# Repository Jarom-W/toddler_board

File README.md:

# Toddler Activity Board

All the files you'd need to 3D print the components, program the hardware, and order the exact PCB I used.

## Some project specifications:

### Hardware
- ESP32 Dev Module

### 3D Printing
- Bambu Lab A1 using standard PLA filament

### Screws
- I used a few different sized screws which I sourced from this lot https://www.amazon.com/dp/B089QX453K?ref=ppx_yo2ov_dt_b_fed_asin_title

### Power Supply
- 4 AA Batteries held inside a battery pack providing ~5V DC to the ESP32 module

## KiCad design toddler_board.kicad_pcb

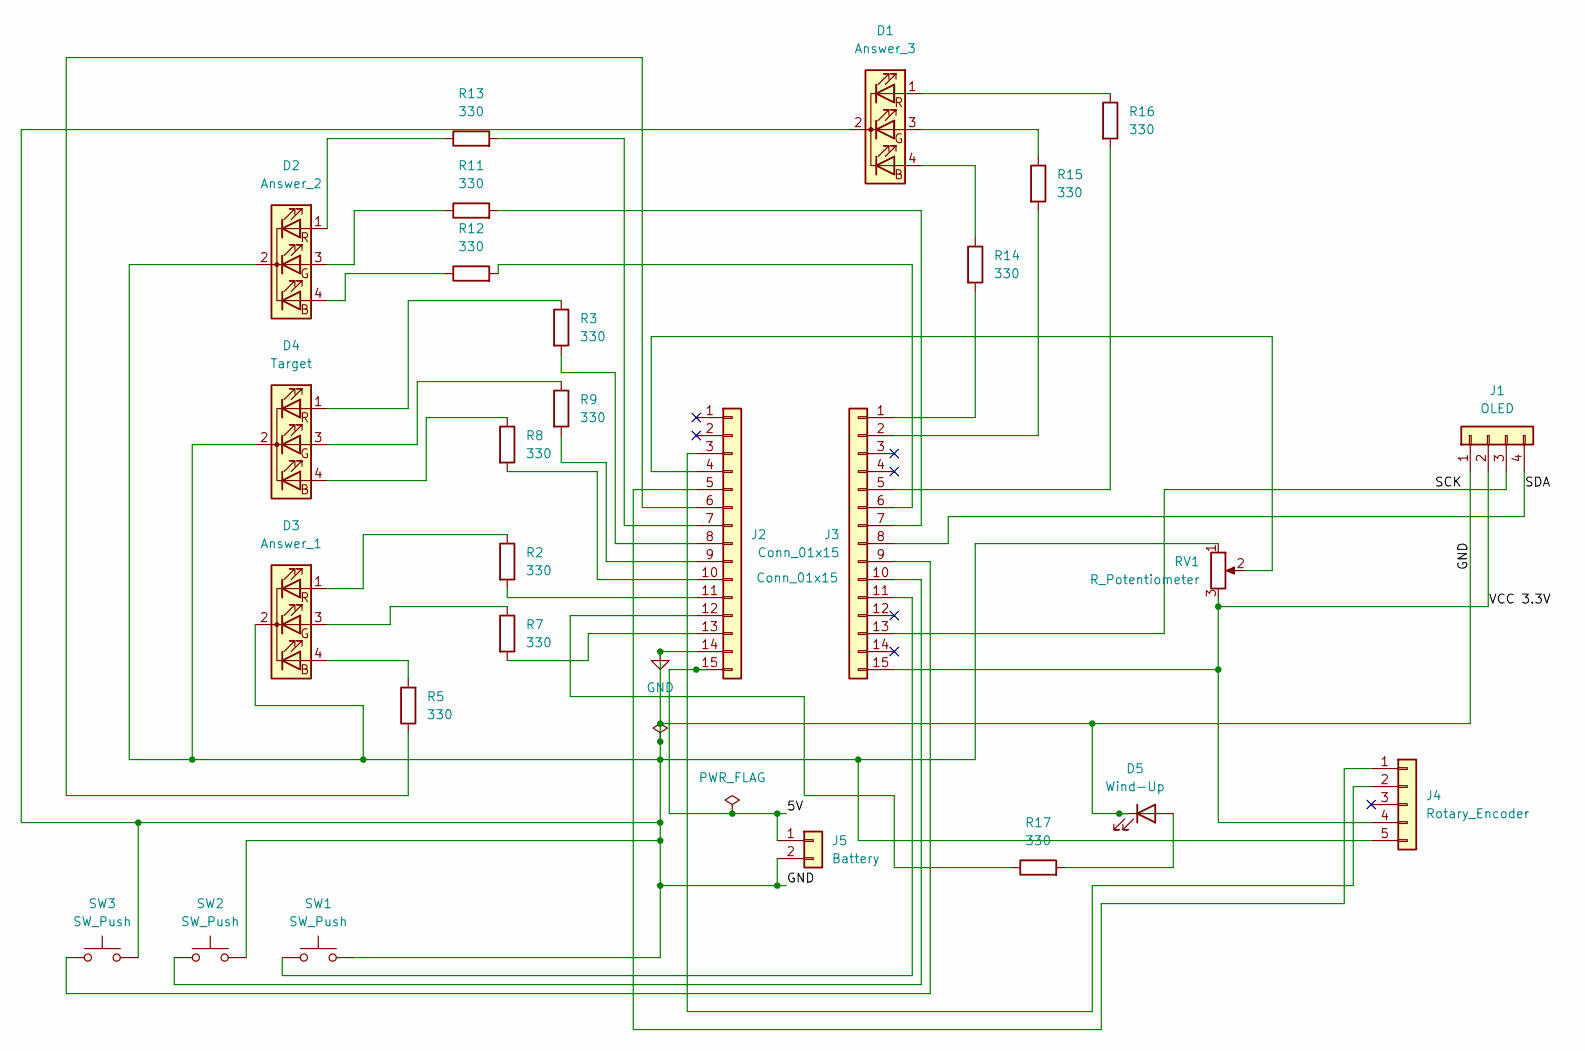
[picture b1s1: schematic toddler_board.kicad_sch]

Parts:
D1: Answer_3; LED_D5.0mm-4_RGB_Wide_Pins
D2: Answer_2; LED_D5.0mm-4_RGB_Wide_Pins
D3: Answer_1; LED_D5.0mm-4_RGB_Wide_Pins
D4: Target; LED_D5.0mm-4_RGB_Wide_Pins
D5: Wind-Up; LED_D5.0mm
J1: OLED; PinSocket_1x04_P2.54mm_Vertical
J2, J3: Conn_01x15; PinSocket_1x15_P2.54mm_Vertical
J4: Rotary_Encoder; PinSocket_1x05_P2.54mm_Vertical
J5: Battery; PinSocket_1x02_P2.54mm_Vertical
R2, R3, R5, R7, R8, R9, R11, R12, R13, R14, R15, R16, R17: 330; R_Axial_DIN0309_L9.0mm_D3.2mm_P12.70mm_Horizontal
RV1: R_Potentiometer; PinSocket_1x03_P2.54mm_Vertical
SW1, SW2, SW3: SW_Push; SW_PUSH_6mm

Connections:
/5V: J2.15, J5.1
/SCK: J1.3, J3.13
/SDA: J1.4, J3.8
/VCC 3.3V: J1.2, J3.15, J4.4, RV1.3
GND: D1.2 (K), D2.2 (K), D3.2 (K), D4.2 (K), D5.1 (K), J1.1, J2.14, J4.5, J5.2, RV1.1, SW1.2, SW2.2, SW3.2
unnamed: D1.4 (BA), R14.1
unnamed: D1.3 (GA), R15.1
unnamed: D1.1 (RA), R16.1
unnamed: D2.4 (BA), R12.1
unnamed: D2.3 (GA), R11.1
unnamed: D2.1 (RA), R13.1
unnamed: D3.4 (BA), R5.2
unnamed: D3.3 (GA), R7.1
unnamed: D3.1 (RA), R2.1
unnamed: D4.4 (BA), R8.1
unnamed: D4.3 (GA), R9.1
unnamed: D4.1 (RA), R3.1
unnamed: D5.2 (A), R17.2
unnamed: J2.3, J4.2
unnamed: J2.4, RV1.2
unnamed: J2.5, J4.1
unnamed: J2.6, R5.1
unnamed: J2.7, R13.2
unnamed: J2.8, R3.2
unnamed: J2.9, R9.2
unnamed: J2.10, R8.2
unnamed: J2.11, R2.2
unnamed: J2.12, R17.1
unnamed: J2.13, R7.2
unnamed: J3.1, R14.2
unnamed: J3.2, R15.2
unnamed: J3.5, R16.2
unnamed: J3.6, R12.2
unnamed: J3.7, R11.2
unnamed: J3.9, SW3.1
unnamed: J3.10, SW2.1
unnamed: J3.11, SW1.1

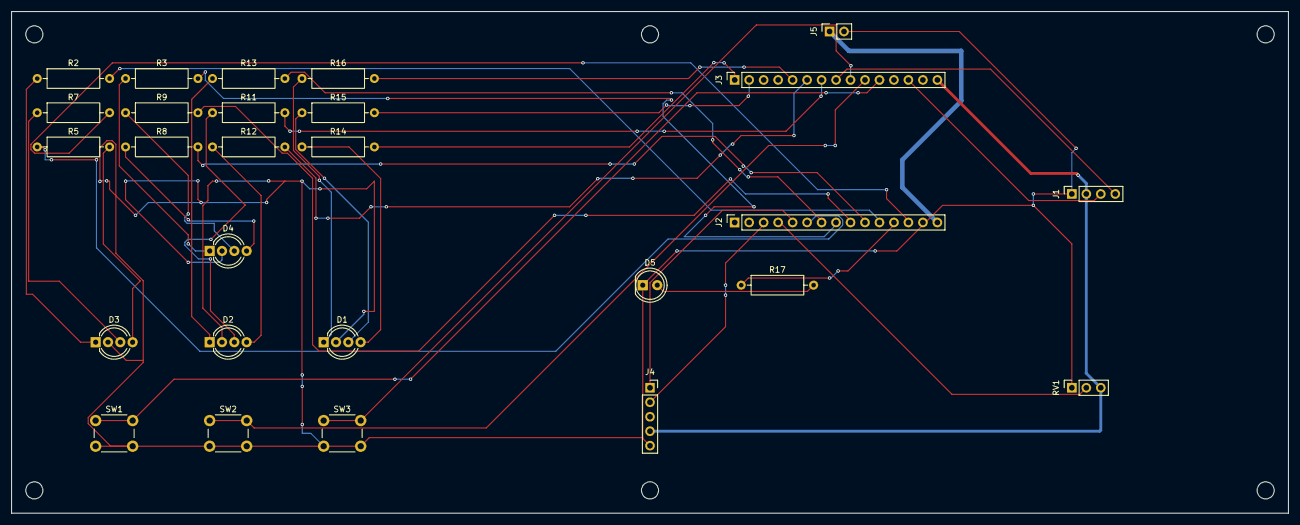
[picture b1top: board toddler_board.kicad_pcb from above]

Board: 2 copper layers, 224.0 x 88.0 mm, 27 parts (0 on the bottom side), 37 nets.
